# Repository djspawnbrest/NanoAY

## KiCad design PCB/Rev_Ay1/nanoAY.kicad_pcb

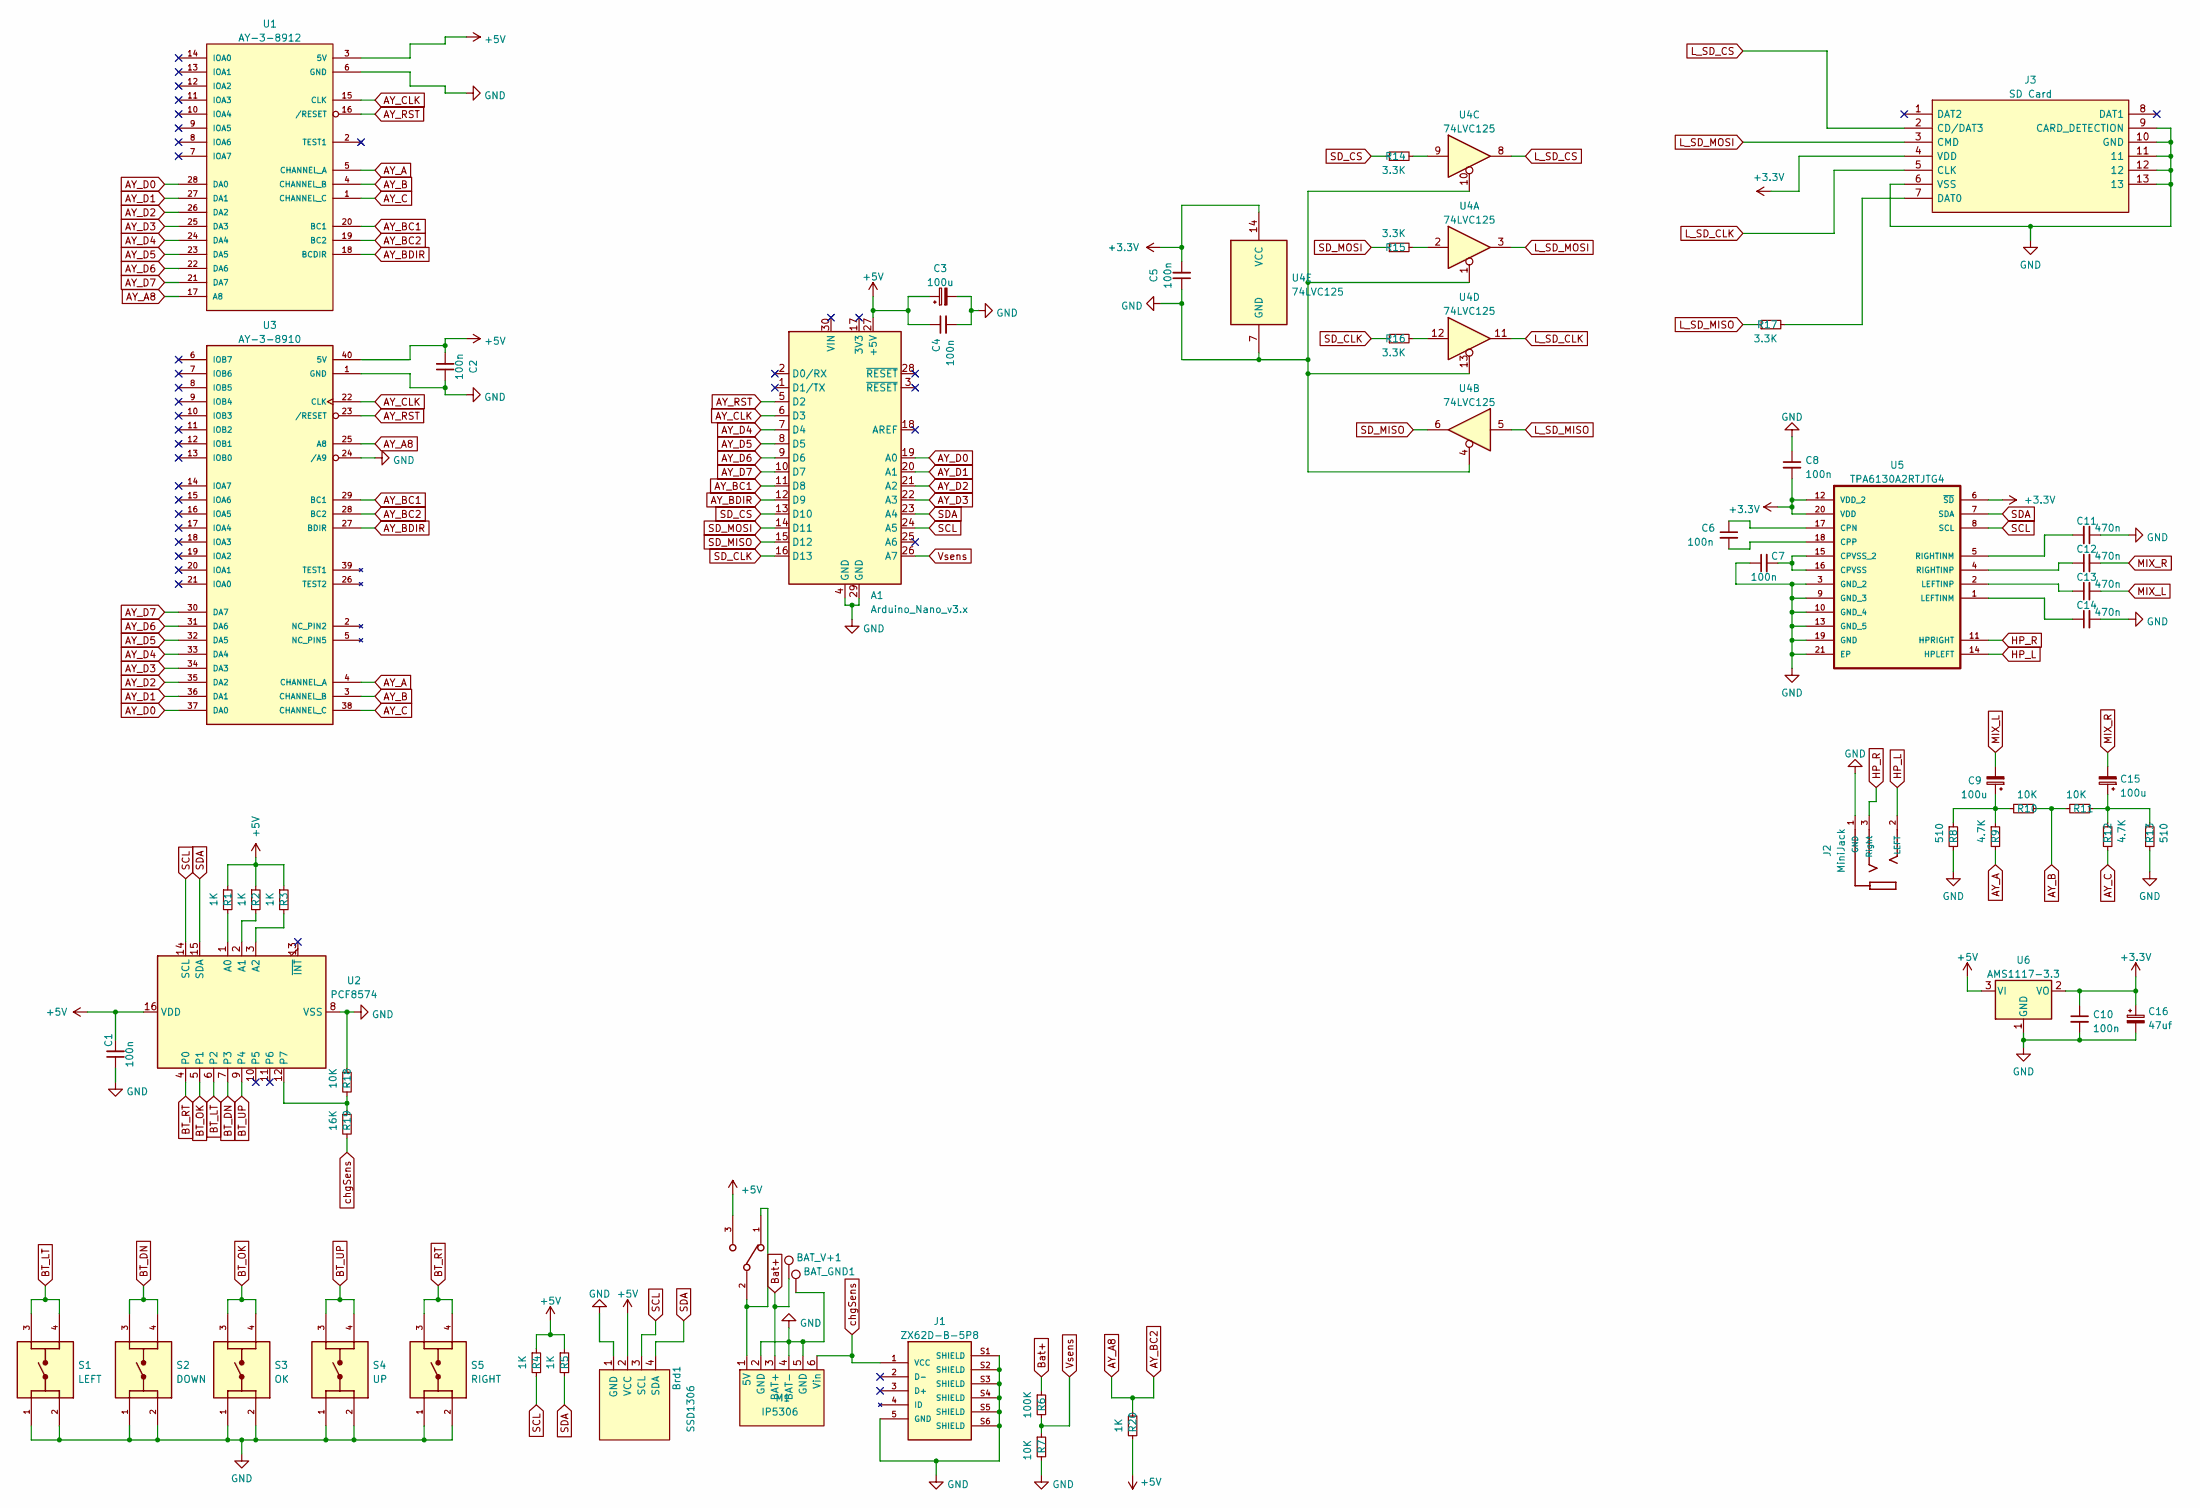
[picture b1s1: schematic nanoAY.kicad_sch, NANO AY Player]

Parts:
A1: Arduino_Nano_v3.x; Arduino_Nano
BAT_GND1: TestPoint; TestPoint_Pad_D3.0mm
BAT_V+1: TestPoint; TestPoint_Pad_D3.0mm
Brd1: SSD1306; 128x64OLED
C1, C2, C4, C5, C6, C7, C8, C10: 100n; C_1206_3216Metric
C3, C9, C15: 100u; CP_EIA-7360-38_Kemet-E
C11, C12, C13, C14: 470n; C_1206_3216Metric
C16: 47uf; CP_EIA-7360-38_Kemet-E
J1: ZX62D-B-5P8; HRS_ZX62D-B-5P8; PARTREV N/A
J2: MiniJack; SWITCHCRAFT_35RAPC2BHN2; PARTREV L
J3: SD Card; TFP09212B; Manufacturer_Part_Number TFP09-2-12B
M1: IP5306; IP5306MODULE
R1, R2, R3, R4, R5, R20: 1K; R_1206_3216Metric
R6: 100K; R_1206_3216Metric
R7, R10, R11, R18: 10K; R_1206_3216Metric
R8, R13: 510; R_1206_3216Metric
R9, R12: 4.7K; R_1206_3216Metric
R14, R15, R16, R17: 3.3K; R_1206_3216Metric
R19: 16K; R_1206_3216Metric
S1: LEFT; SW_1825910-7
S2: DOWN; SW_1825910-7
S3: OK; SW_1825910-7
S4: UP; SW_1825910-7
S5: RIGHT; SW_1825910-7
S6: EG1213; SW_EG1213
U1: AY-3-8912; DIP-28_W15.24mm_Socket
U2: PCF8574; SOIC-16_3.9x9.9mm_P1.27mm
U3: AY-3-8910; DIP-40_W15.24mm_Socket
U4: 74LVC125; TSSOP-14_4.4x5mm_P0.65mm
U5: TPA6130A2RTJTG4; QFN50P400X400X80-21N; MPN TPA6130A2RTJTG4
U6: AMS1117-3.3; SOT-223-3_TabPin2

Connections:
+3.3V: C5.2, C8.2, C10.1, C16.1, J3.4 (VDD), U4.14 (VCC), U5.6 (~SD), U5.12 (VDD_2), U5.20 (VDD), U6.2 (VO)
+5V: A1.27 (+5V), Brd1.2 (VCC), C1.2, C2.2, C3.1, C4.1, R1.1, R2.1, R3.1, R4.1, R5.1, R20.2, S6.3, U1.3 (5V), U2.16 (VDD), U3.40 (5V), U6.3 (VI)
AY_A: R9.2, U1.5 (CHANNEL_A), U3.4 (CHANNEL_A)
AY_A8: R20.1, U1.17 (A8), U1.19 (BC2), U3.25 (A8), U3.28 (BC2)
AY_B: R10.1, R11.2, U1.4 (CHANNEL_B), U3.3 (CHANNEL_B)
AY_BC1: A1.11 (D8), U1.20 (BC1), U3.29 (BC1)
AY_BDIR: A1.12 (D9), U1.18 (BCDIR), U3.27 (BDIR)
AY_C: R12.2, U1.1 (CHANNEL_C), U3.38 (CHANNEL_C)
AY_CLK: A1.6 (D3), U1.15 (CLK), U3.22 (CLK)
AY_D0: A1.19 (A0), U1.28 (DA0), U3.37 (DA0)
AY_D1: A1.20 (A1), U1.27 (DA1), U3.36 (DA1)
AY_D2: A1.21 (A2), U1.26 (DA2), U3.35 (DA2)
AY_D3: A1.22 (A3), U1.25 (DA3), U3.34 (DA3)
AY_D4: A1.7 (D4), U1.24 (DA4), U3.33 (DA4)
AY_D5: A1.8 (D5), U1.23 (DA5), U3.32 (DA5)
AY_D6: A1.9 (D6), U1.22 (DA6), U3.31 (DA6)
AY_D7: A1.10 (D7), U1.21 (DA7), U3.30 (DA7)
AY_RST: A1.5 (D2), U1.16 (/RESET), U3.23 (/RESET)
BT_DN: S2.3, S2.4, U2.7 (P3)
BT_LT: S1.3, S1.4, U2.6 (P2)
BT_OK: S3.3, S3.4, U2.5 (P1)
BT_RT: S5.3, S5.4, U2.4 (P0)
BT_UP: S4.3, S4.4, U2.9 (P4)
Bat+: BAT_V+1.1, M1.3 (BAT+), R6.1; also elsewhere on the board
GND: A1.4 (GND), A1.29 (GND), BAT_GND1.1, Brd1.1 (GND), C1.1, C2.1, C3.2, C4.2, C5.1, C7.1, C8.1, C10.2, C11.1, C14.2, C16.2, J1.5 (GND), J1.S1 (SHIELD), J1.S2 (SHIELD), J1.S3 (SHIELD), J1.S4 (SHIELD), J1.S5 (SHIELD), J1.S6 (SHIELD), J2.1 (GND), J3.6 (VSS), J3.9 (CARD_DETECTION), J3.10 (GND), J3.11, J3.12, J3.13, M1.2 (GND), M1.4 (BAT-), M1.5 (GND), R7.2, R8.2, R13.2, R18.1, S1.1, S1.2, S2.1, S2.2, S3.1, S3.2, S4.1, S4.2, S5.1, S5.2, U1.6 (GND), U2.8 (VSS), U3.1 (GND), U3.24 (/A9), U4.1, U4.4, U4.7 (GND), U4.10, U4.13, U5.3 (GND_2), U5.9 (GND_3), U5.10 (GND_4), U5.13 (GND_5), U5.19 (GND), U5.21 (EP), U6.1 (GND); also elsewhere on the board
HP_L: J2.2 (LEFT), U5.14 (HPLEFT)
HP_R: J2.3 (Right), U5.11 (HPRIGHT)
L_SD_CLK: J3.5 (CLK), U4.11
L_SD_CS: J3.2 (CD/DAT3), U4.8
L_SD_MISO: R17.1, U4.5
L_SD_MOSI: J3.3 (CMD), U4.3
MIX_L: C9.2, C13.2
MIX_R: C12.2, C15.2
unnamed: C6.1, U5.17 (CPN)
unnamed: C6.2, U5.18 (CPP)
unnamed: C7.2, U5.15 (CPVSS_2), U5.16 (CPVSS)
unnamed: C9.1, R8.1, R9.1, R10.2
unnamed: C11.2, U5.5 (RIGHTINM)
unnamed: C12.1, U5.4 (RIGHTINP)
unnamed: C13.1, U5.2 (LEFTINP)
unnamed: C14.1, U5.1 (LEFTINM)
unnamed: C15.1, R11.1, R12.1, R13.1
unnamed: J3.7 (DAT0), R17.2
unnamed: M1.1 (5V), S6.1, S6.2
unnamed: R1.2, U2.1 (A0)
unnamed: R2.2, U2.2 (A1)
unnamed: R3.2, U2.3 (A2)
unnamed: R14.2, U4.9
unnamed: R15.2, U4.2
unnamed: R16.2, U4.12
unnamed: R18.2, R19.1, U2.12 (P7)
SCL: A1.24 (A5), Brd1.3 (SCL), R4.2, U2.14 (SCL), U5.8 (SCL)
SDA: A1.23 (A4), Brd1.4 (SDA), R5.2, U2.15 (SDA), U5.7 (SDA)
SD_CLK: A1.16 (D13), R16.1
SD_CS: A1.13 (D10), R14.1
SD_MISO: A1.15 (D12), U4.6
SD_MOSI: A1.14 (D11), R15.1
Vsens: A1.26 (A7), R6.2, R7.1
chgSens: J1.1 (VCC), M1.6 (Vin), R19.2

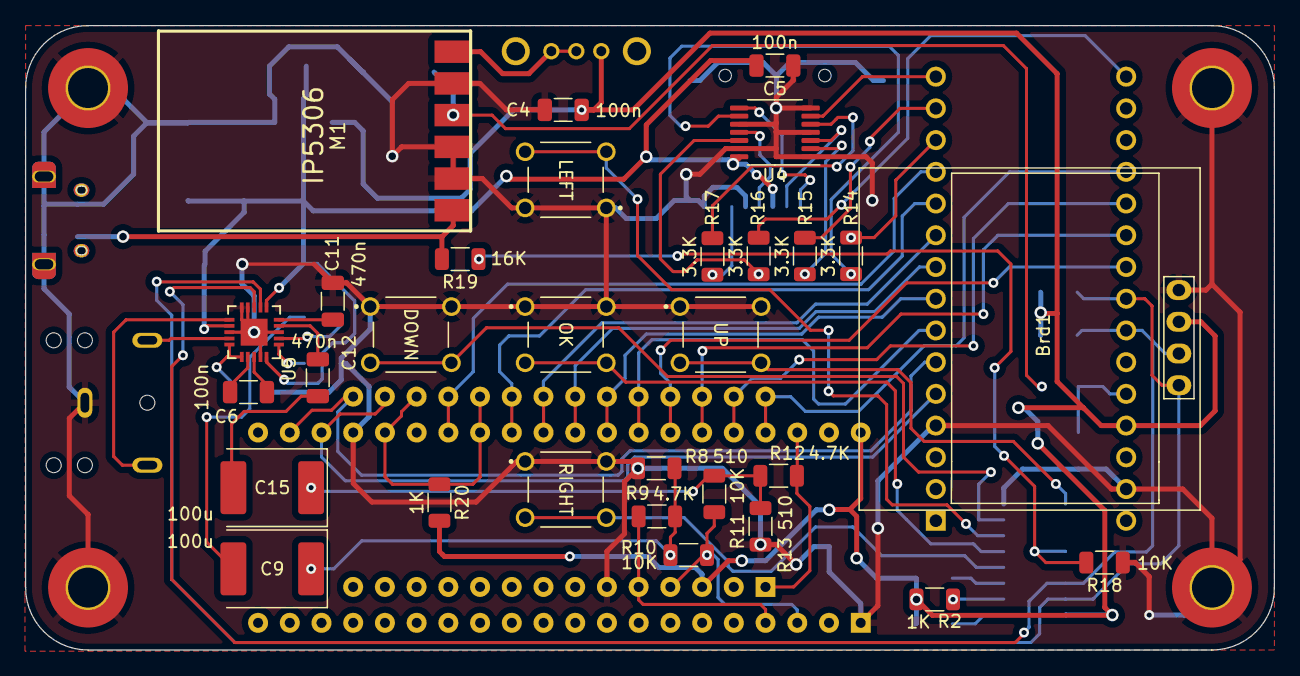
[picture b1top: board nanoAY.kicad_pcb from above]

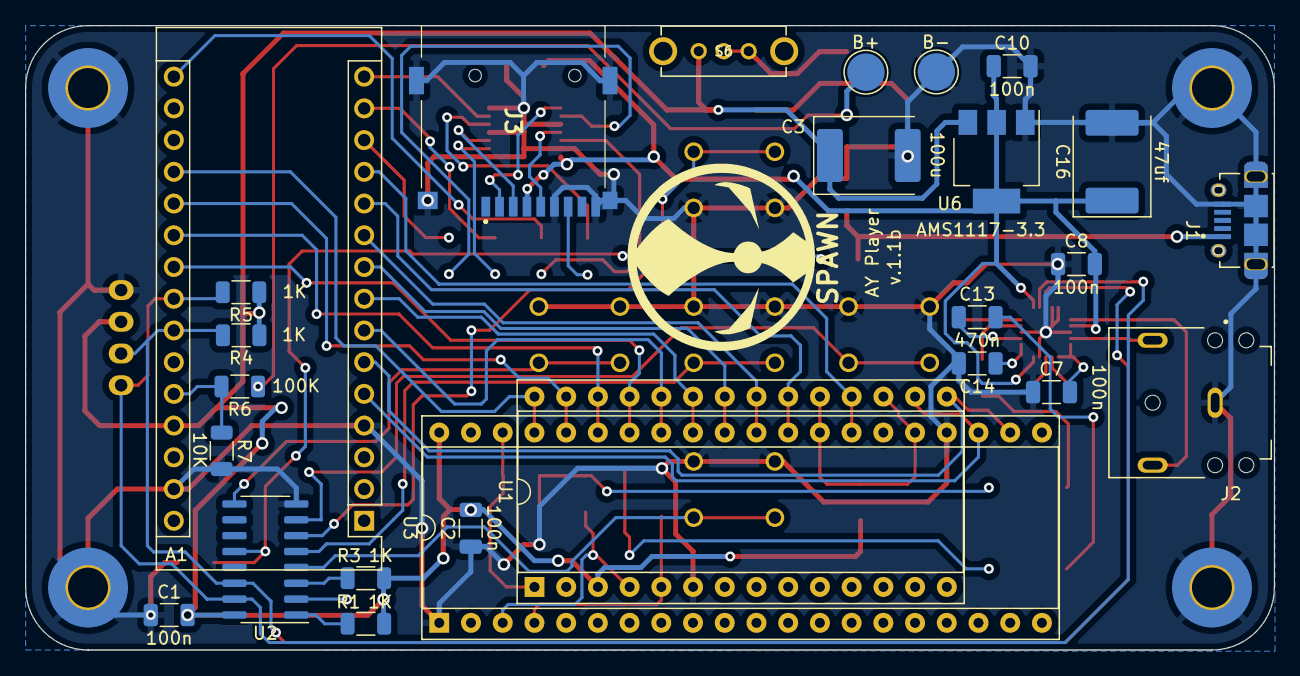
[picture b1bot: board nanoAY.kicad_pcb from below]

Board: 2 copper layers, 100.0 x 50.0 mm, 57 parts (27 on the bottom side), 59 nets.

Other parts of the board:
B+: TestPoint; TestPoint_Pad_D3.0mm
B-: TestPoint; TestPoint_Pad_D3.0mm
by SPAWN: LOGO; spawnllogo

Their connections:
Bat+: B+.1; also elsewhere on the board
GND: B-.1; also elsewhere on the board

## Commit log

2022-11-21 init commit
2022-11-21 add: firmware
2022-11-21 add: case for 3D print
2022-11-21 refactor: firmware to folder
2022-11-21 add: PCB and gerbers
2022-11-21 add: Schematic
2022-11-21 add: some Renders
